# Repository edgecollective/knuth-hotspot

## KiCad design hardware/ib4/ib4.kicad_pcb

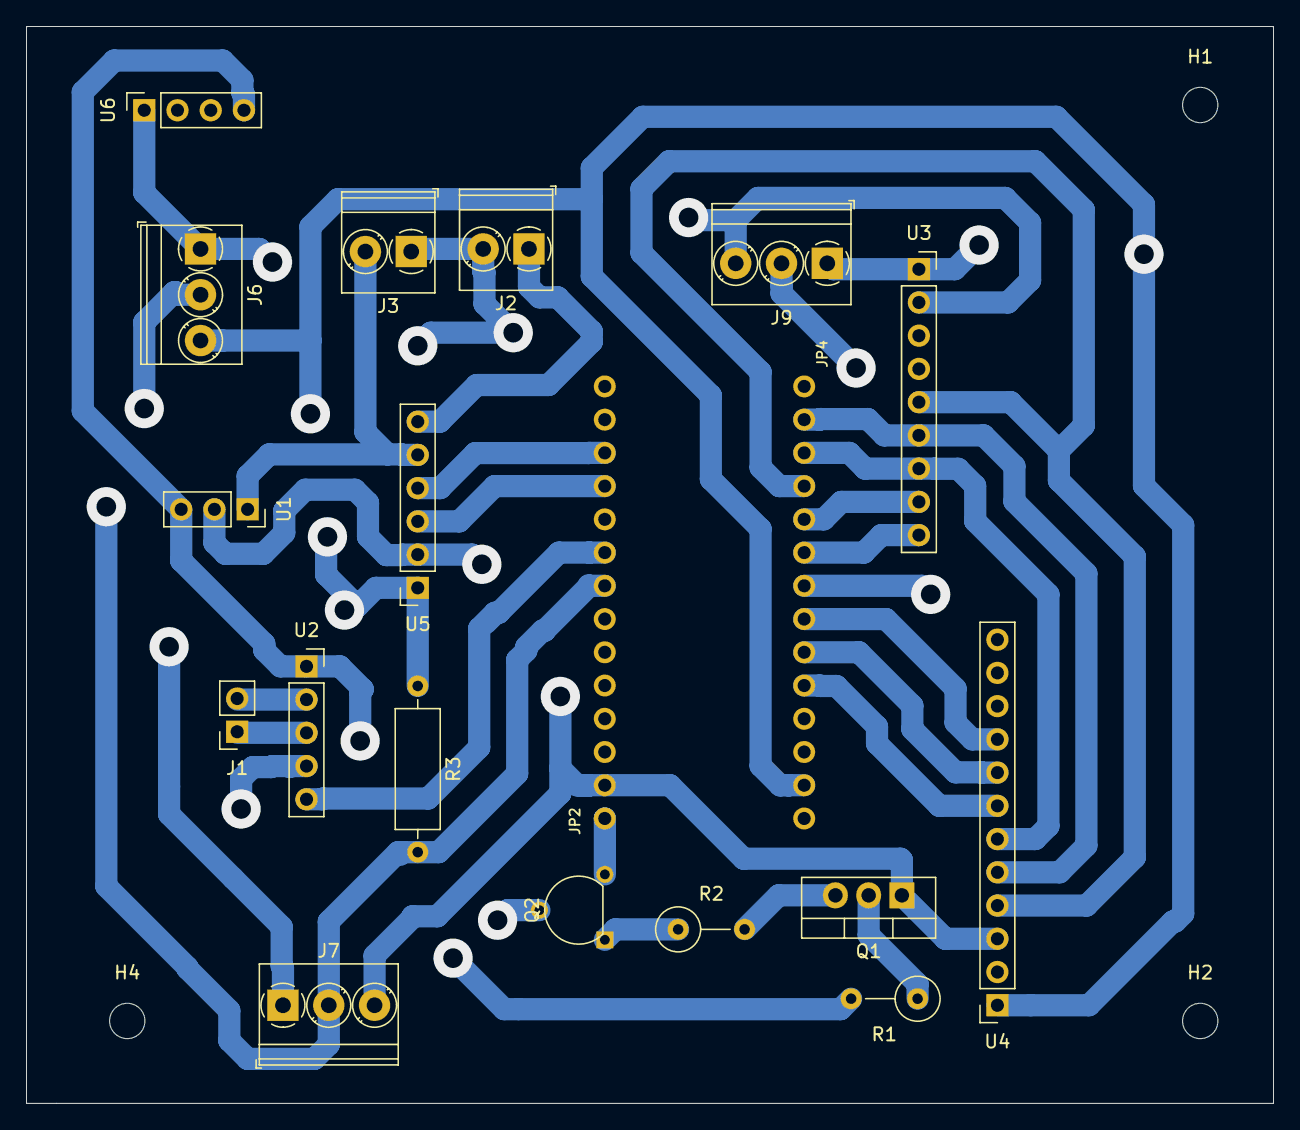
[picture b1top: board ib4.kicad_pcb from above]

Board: 4 copper layers, 95.3 x 82.3 mm, 22 parts (0 on the bottom side), 24 nets.

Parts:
H1, H2, H4: MountingHole; MountingHole_2.7mm_M2.5
J1: Conn_01x02_Female; PinSocket_1x02_P2.54mm_Vertical
J2, J3: Screw_Terminal_01x02; TerminalBlock_Phoenix_PT-1,5-2-3.5-H_1x02_P3.50mm_Horizontal
J6, J7, J9: Screw_Terminal_01x03; TerminalBlock_Phoenix_PT-1,5-3-3.5-H_1x03_P3.50mm_Horizontal
JP2, JP4: HEADER-1X14; 1X14_ROUND70
Q1: Q_NPN_EBC; TO-220-3_Vertical
Q2: Q_PNP_BCE; TO-92
R1, R2: R; R_Axial_DIN0309_L9.0mm_D3.2mm_P5.08mm_Vertical
R3: R; R_Axial_DIN0309_L9.0mm_D3.2mm_P12.70mm_Horizontal
U1: DC-DC_5V_TSR_1-22450; PinSocket_1x03_P2.54mm_Vertical
U2: tpl5110; PinSocket_1x05_P2.54mm_Vertical
U3: lora_breakout; PinSocket_1x09_P2.54mm_Vertical
U4: adafruit_esp32airlift_breakout; PinSocket_1x12_P2.54mm_Vertical
U5: adafruit_ina219; PinSocket_1x06_P2.54mm_Vertical
U6: adafruit_USB_part; PinSocket_1x04_P2.54mm_Vertical

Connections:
5V_BUCK: Q2.2, U1.3, U2.1, U6.4
5V_SWITCHED: JP2.1, Q2.3
12V_BATTERY: J3.2, U1.1, U5.5
+3V3: J6.3, J7.1, J9.1, JP4.13, R3.1, U3.1, U4.1, U5.1
A3: J9.2, JP4.7
D9: J6.2, J7.2, JP2.8, R3.2
DONE: JP2.9, U2.5
E_BUSY: JP4.9, U4.8
E_CS: JP4.10, U4.7
E_RST: JP4.8, U4.9
GND: J1.2, J2.2, J3.1, J6.1, J7.3, J9.3, JP2.2, Q1.1, U1.2, U2.2, U3.2, U4.3, U5.2, U6.1
LORA_CS: JP4.5, U3.8
LORA_RST: JP4.6, U3.9
MISO: JP4.2, U3.6, U4.5
MOSI: JP4.3, U3.7, U4.6
unnamed: J1.1, U2.3
unnamed: Q1.2, R1.1
unnamed: Q1.3, R2.2
unnamed: Q2.1, R2.1
SCK: JP4.4, U3.5, U4.4
SCL: JP2.11, U5.3
SDA: JP2.12, U5.4
SOLAR_CONTROLLER: J2.1, U5.6
TIMER: R1.2, U2.4

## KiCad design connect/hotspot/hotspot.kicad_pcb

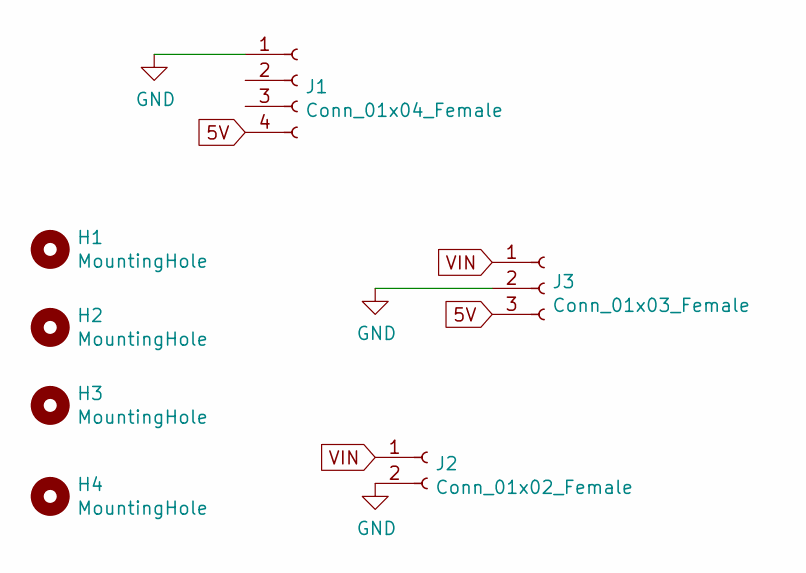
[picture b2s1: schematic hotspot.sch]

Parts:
H1, H2, H3, H4: MountingHole; MountingHole_2.7mm_M2.5
J1: Conn_01x04_Female; PinSocket_1x04_P2.54mm_Vertical
J2: Conn_01x02_Female; TerminalBlock_Phoenix_PT-1,5-2-3.5-H_1x02_P3.50mm_Horizontal
J3: Conn_01x03_Female; PinSocket_1x03_P2.54mm_Vertical

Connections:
5V: J1.4, J3.3
GND: J1.1, J2.2, J3.2
VIN: J2.1, J3.1

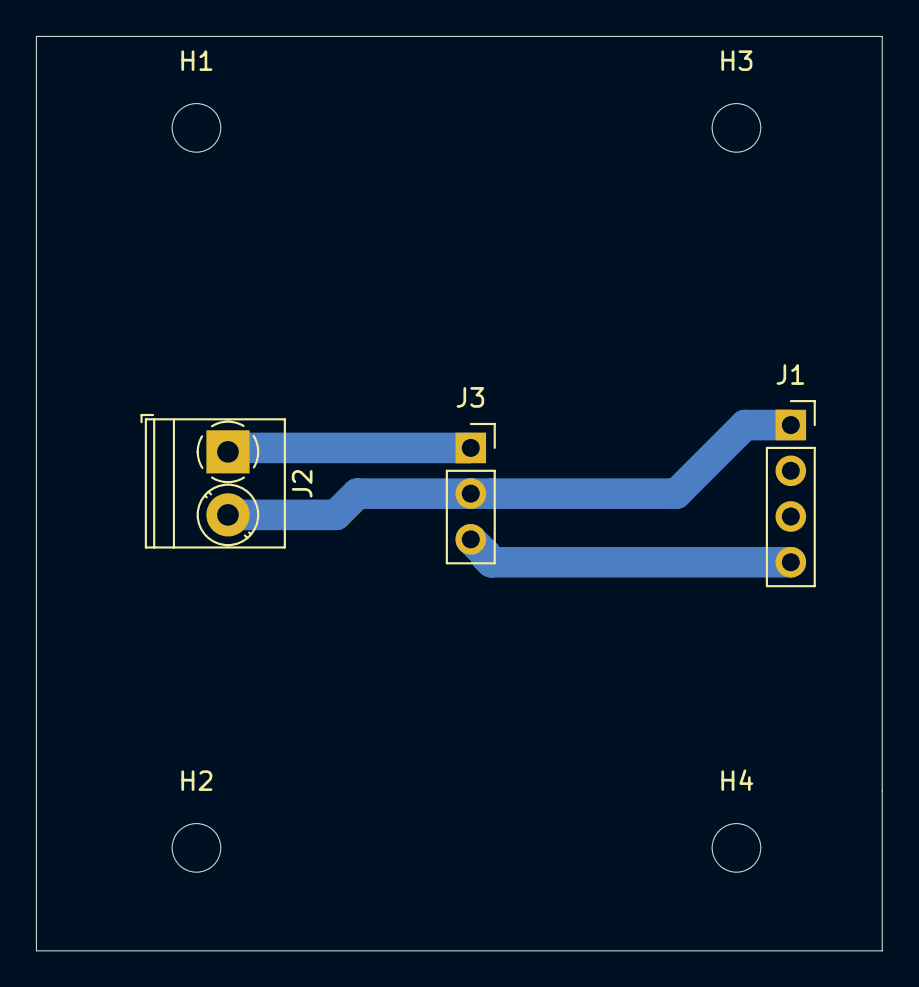
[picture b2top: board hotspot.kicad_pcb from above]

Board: 2 copper layers, 47.0 x 50.8 mm, 7 parts (0 on the bottom side), 3 nets.

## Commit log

2019-11-02 nearly done with layout
